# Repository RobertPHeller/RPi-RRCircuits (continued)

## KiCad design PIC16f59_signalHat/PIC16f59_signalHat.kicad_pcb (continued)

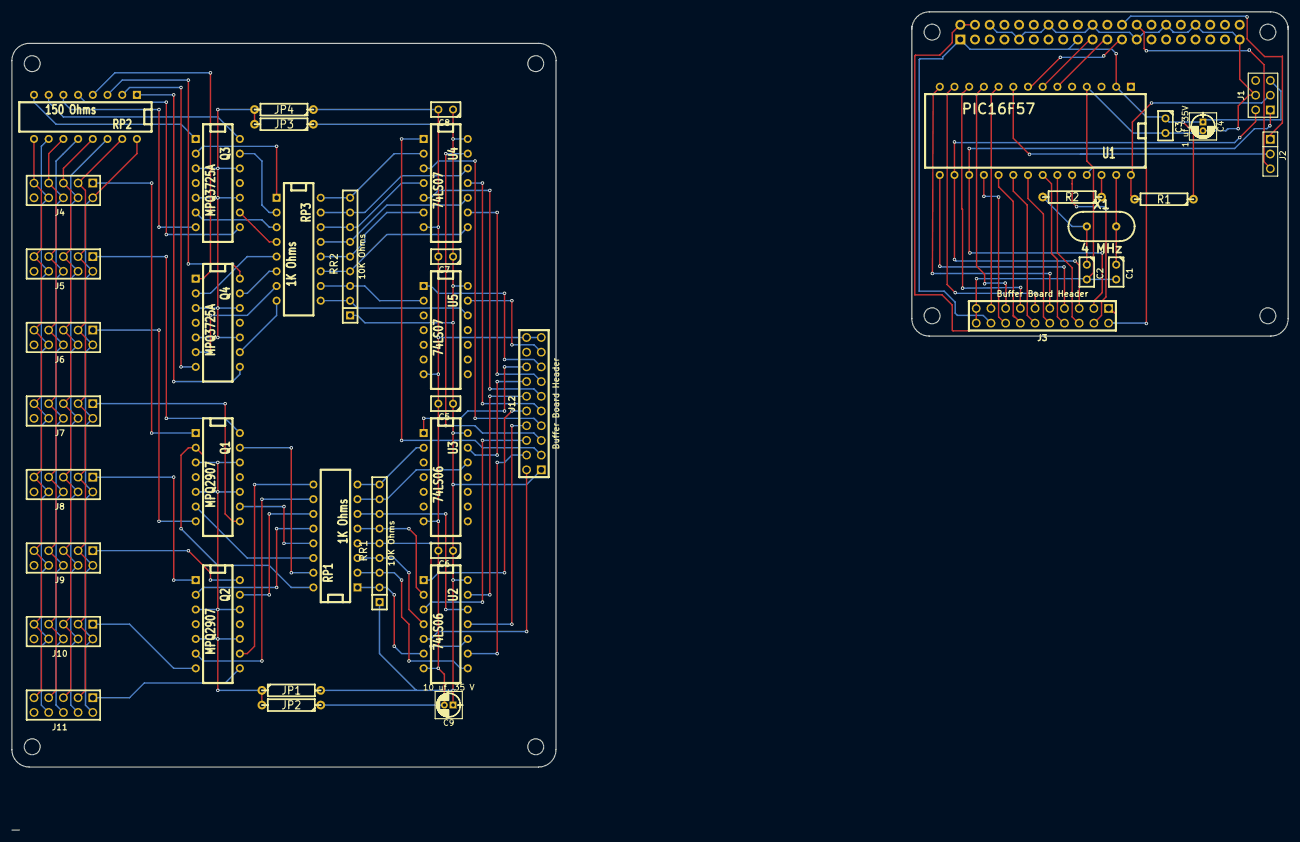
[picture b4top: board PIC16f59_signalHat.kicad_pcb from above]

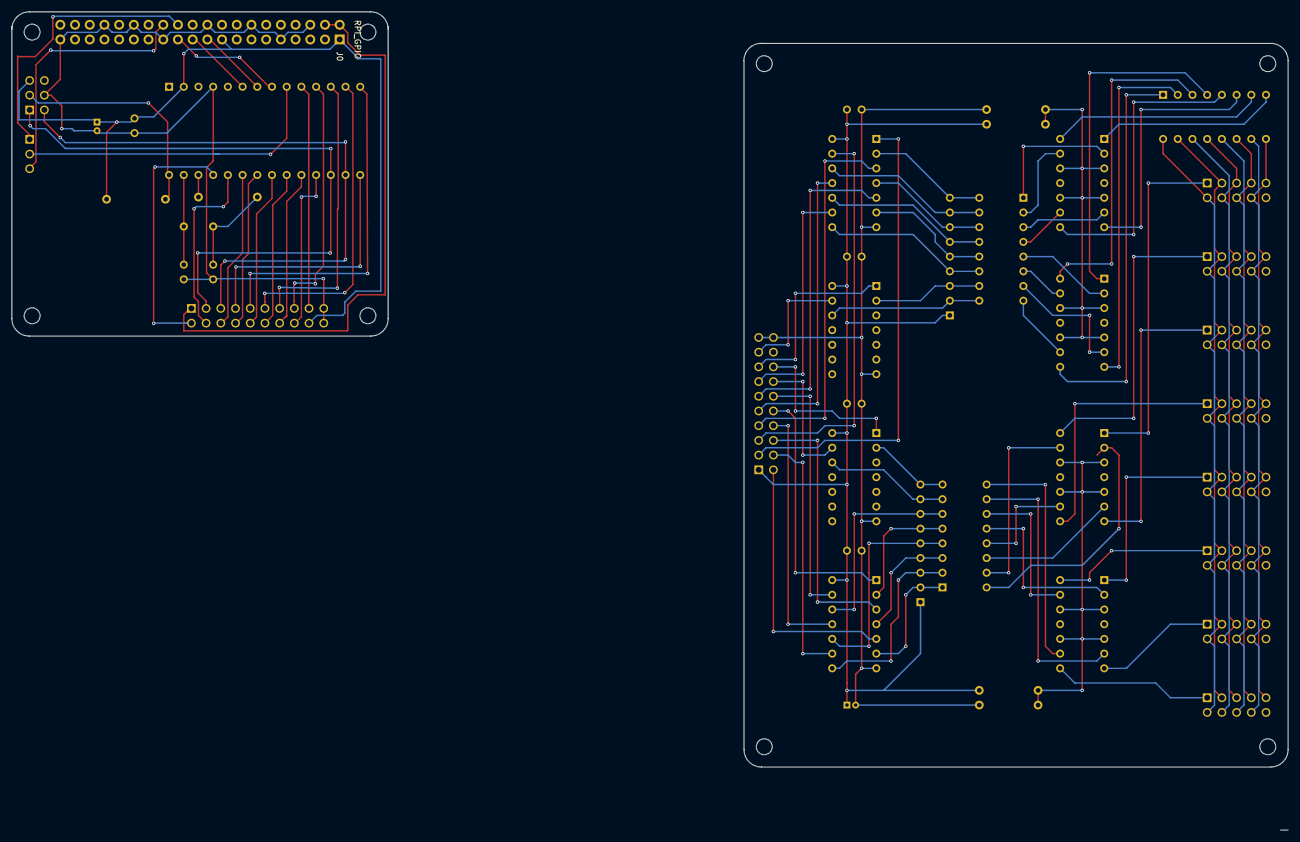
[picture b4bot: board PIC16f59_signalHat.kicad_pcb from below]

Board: 2 copper layers, 220.5 x 141.3 mm, 51 parts (9 on the bottom side), 105 nets.

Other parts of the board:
H1, H2, H3, H4, H4#2, H4#3, H4#4, H4#5: RPi_Hat_Mounting_Hole

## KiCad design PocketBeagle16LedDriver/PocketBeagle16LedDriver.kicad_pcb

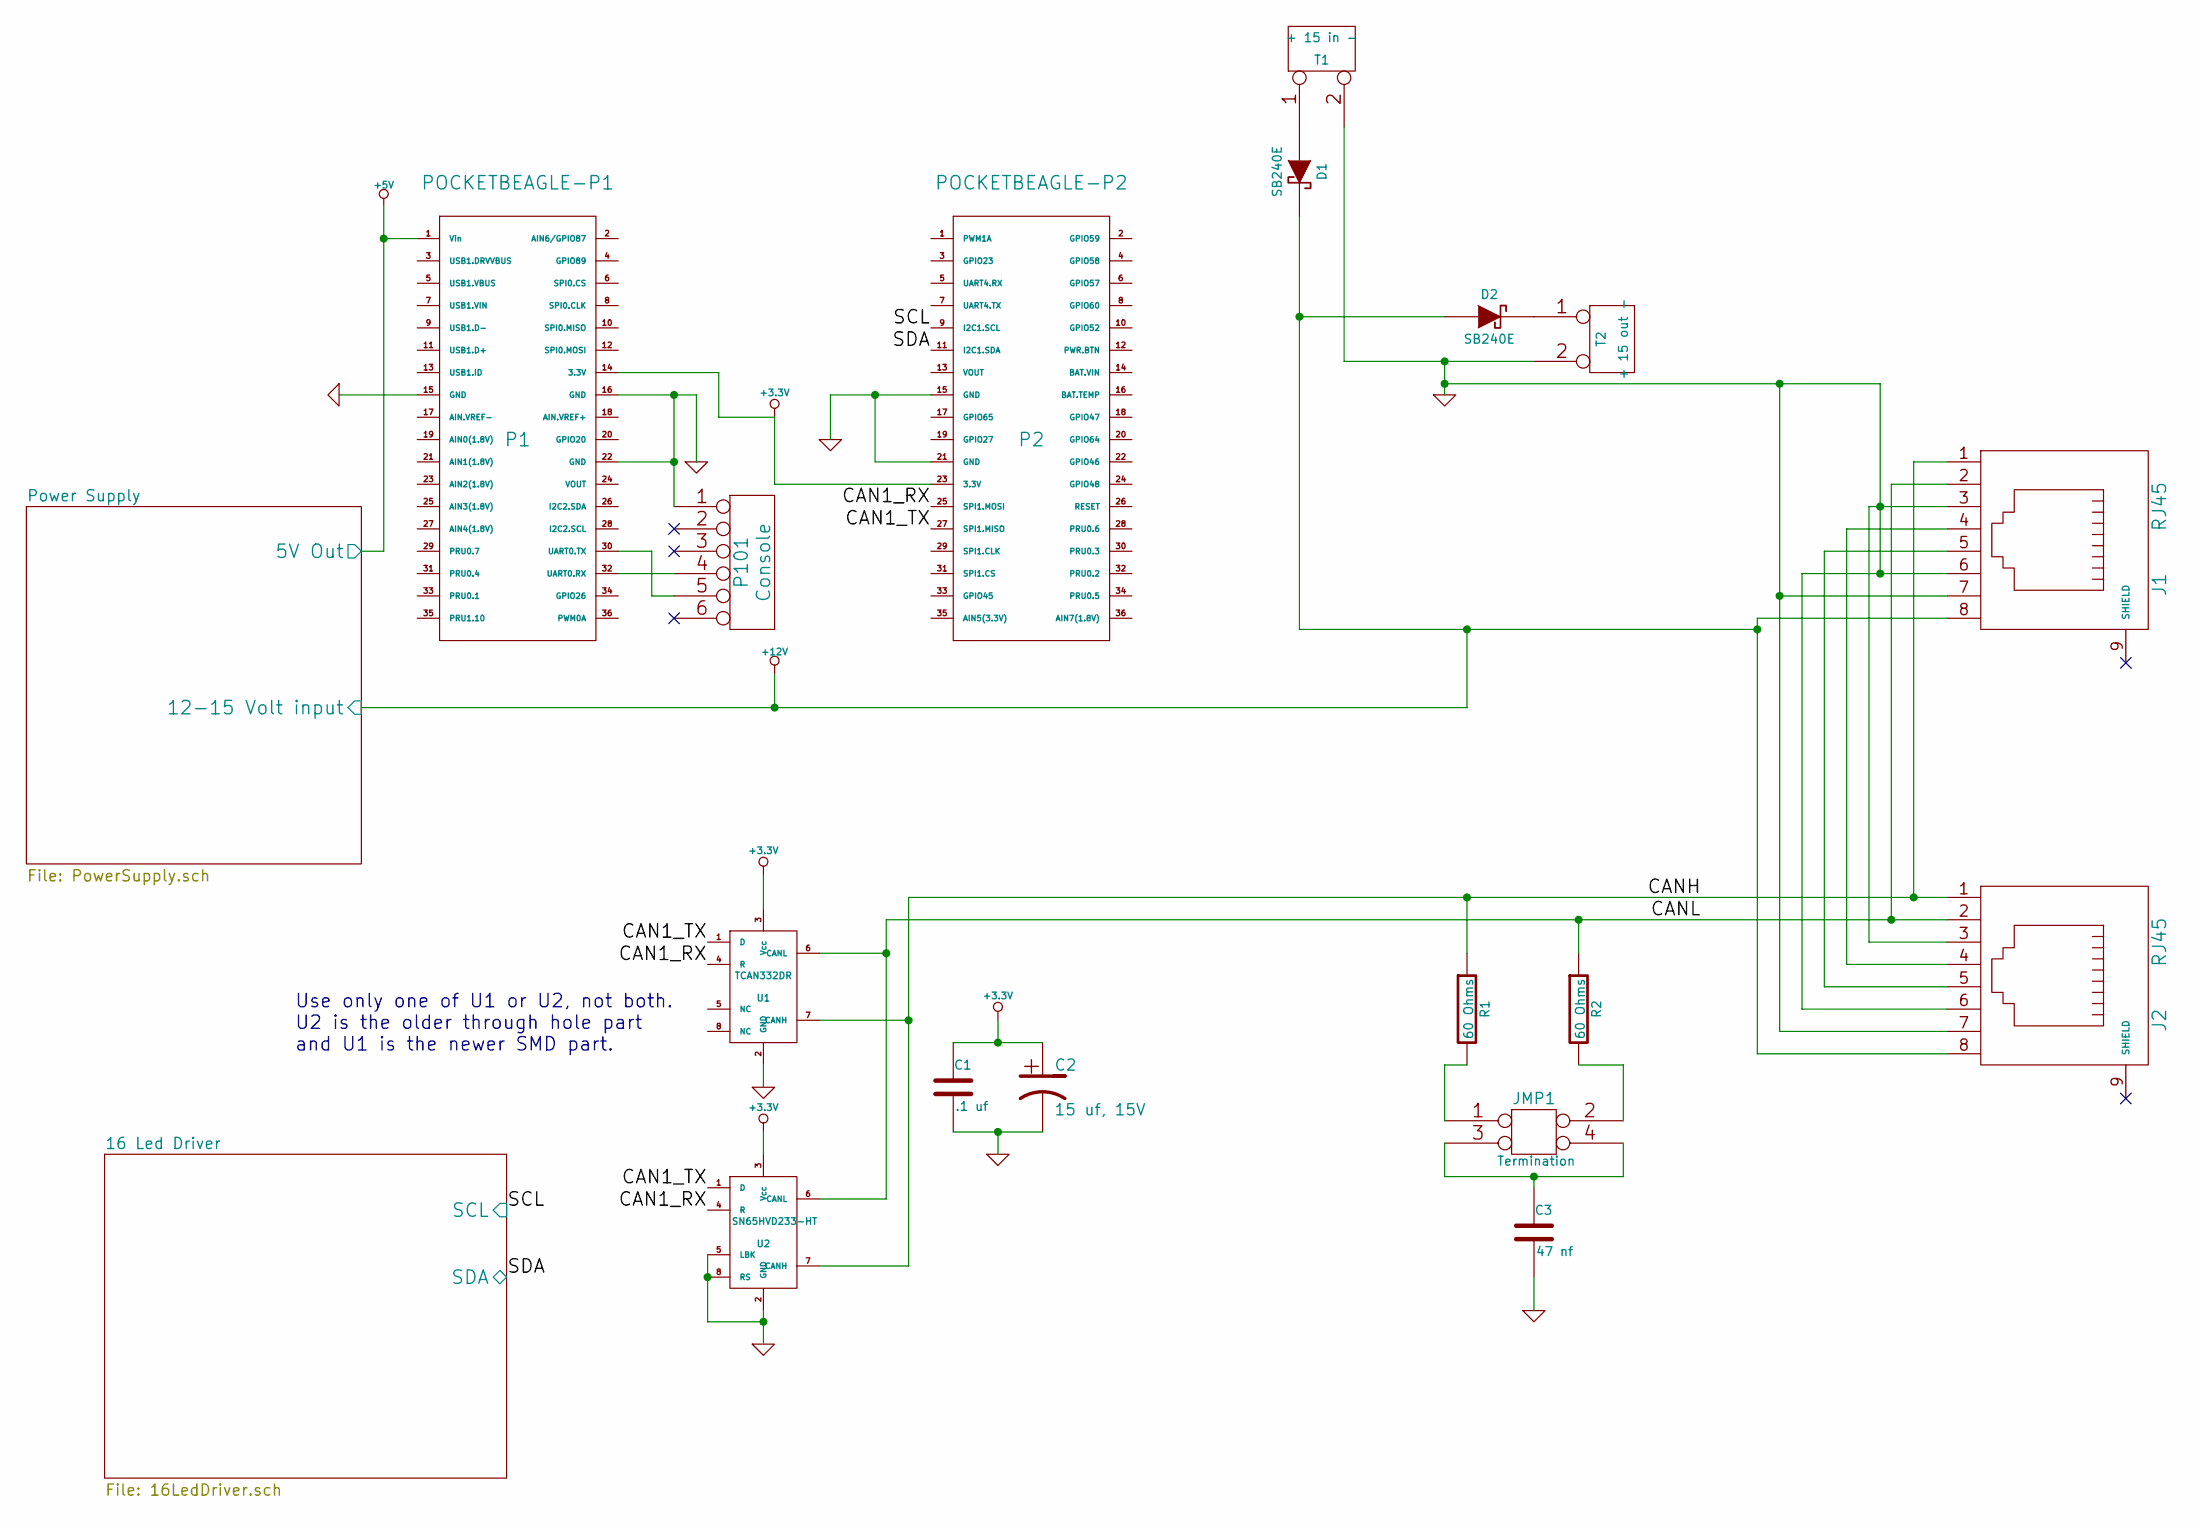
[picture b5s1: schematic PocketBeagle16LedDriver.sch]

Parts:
C1: .1 uf
C2: 15 uf, 15V
C3: 47 nf
D1, D2: SB240E
J1, J2: RJ45
JMP1: Termination
P1: POCKETBEAGLE-P1
P2: POCKETBEAGLE-P2
P101: Console
R1, R2: 60 Ohms
T1: + 15 in -
T2: + 15 out -
U1: TCAN332DR
U2: SN65HVD233-HT

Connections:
+3.3V: C1.1, C2.1, P1.14 (3.3V), P2.23 (3.3V), U1.3 (Vcc), U2.3 (Vcc); also elsewhere on the board
+5V: P1.1 (Vin); also elsewhere on the board
+12V: D1.2 (K), D2.1 (A), J1.8, J2.8; also elsewhere on the board
/16 Led Driver/SCL: P2.9 (I2C1.SCL); also elsewhere on the board
/16 Led Driver/SDA: P2.11 (I2C1.SDA); also elsewhere on the board
/CAN1_RX: P2.25 (SPI1.MOSI), U1.4 (R), U2.4 (R)
/CAN1_TX: P2.27 (SPI1.MISO), U1.1 (D), U2.1 (D)
/CANH: J1.1, J2.1, R1.1, U1.7 (CANH), U2.7 (CANH)
/CANL: J1.2, J2.2, R2.1, U1.6 (CANL), U2.6 (CANL)
GND: C1.2, C2.2, C3.2, J1.3, J1.6, J1.7, J2.3, J2.6, J2.7, P1.15 (GND), P1.16 (GND), P1.22 (GND), P2.15 (GND), P2.21 (GND), P101.1, T1.2 (PM), T2.2 (PM), U1.2 (GND), U2.2 (GND), U2.5 (LBK), U2.8 (RS); also elsewhere on the board
unnamed: J1.4, J2.4
unnamed: J1.5, J2.5
unnamed: P1.32 (UART0.RX), P101.4
unnamed: P1.30 (UART0.TX), P101.5
unnamed: JMP1.1, R1.2
unnamed: JMP1.2, R2.2
unnamed: C3.1, JMP1.3, JMP1.4
unnamed: D1.1 (A), T1.1
unnamed: D2.2 (K), T2.1

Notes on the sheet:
Use only one of U1 or U2, not both. U2 is the older through hole part and U1 is the newer SMD part.

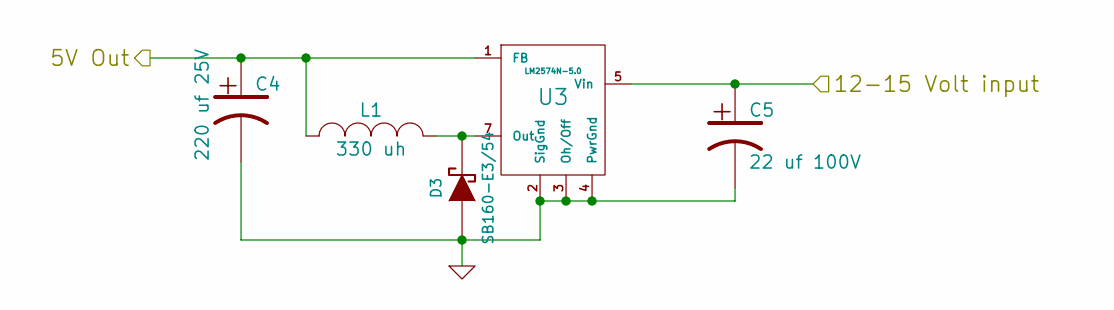
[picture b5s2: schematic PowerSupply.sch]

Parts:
C4: 220 uf 25V; C1-3V8; Part Number REA221M1EBK-0811P
C5: 22 uf 100V; C1-3V8; Part Number REA220M2ABK-0811P
D3: SB160-E3/54; DO-41; Part Number SB160-E3/54
L1: 330 uh; PE-LowProfile; Part Number PE-52627NL
U3: LM2574N-5.0

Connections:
+5V: C4.1, L1.1, U3.1 (FB); also elsewhere on the board
+12V: C5.1, U3.5 (Vin); also elsewhere on the board
GND: C4.2, C5.2, D3.1 (A), U3.2 (SigGnd), U3.3 (Oh/Off), U3.4 (PwrGnd); also elsewhere on the board
unnamed: D3.2 (K), L1.2, U3.7 (Out)

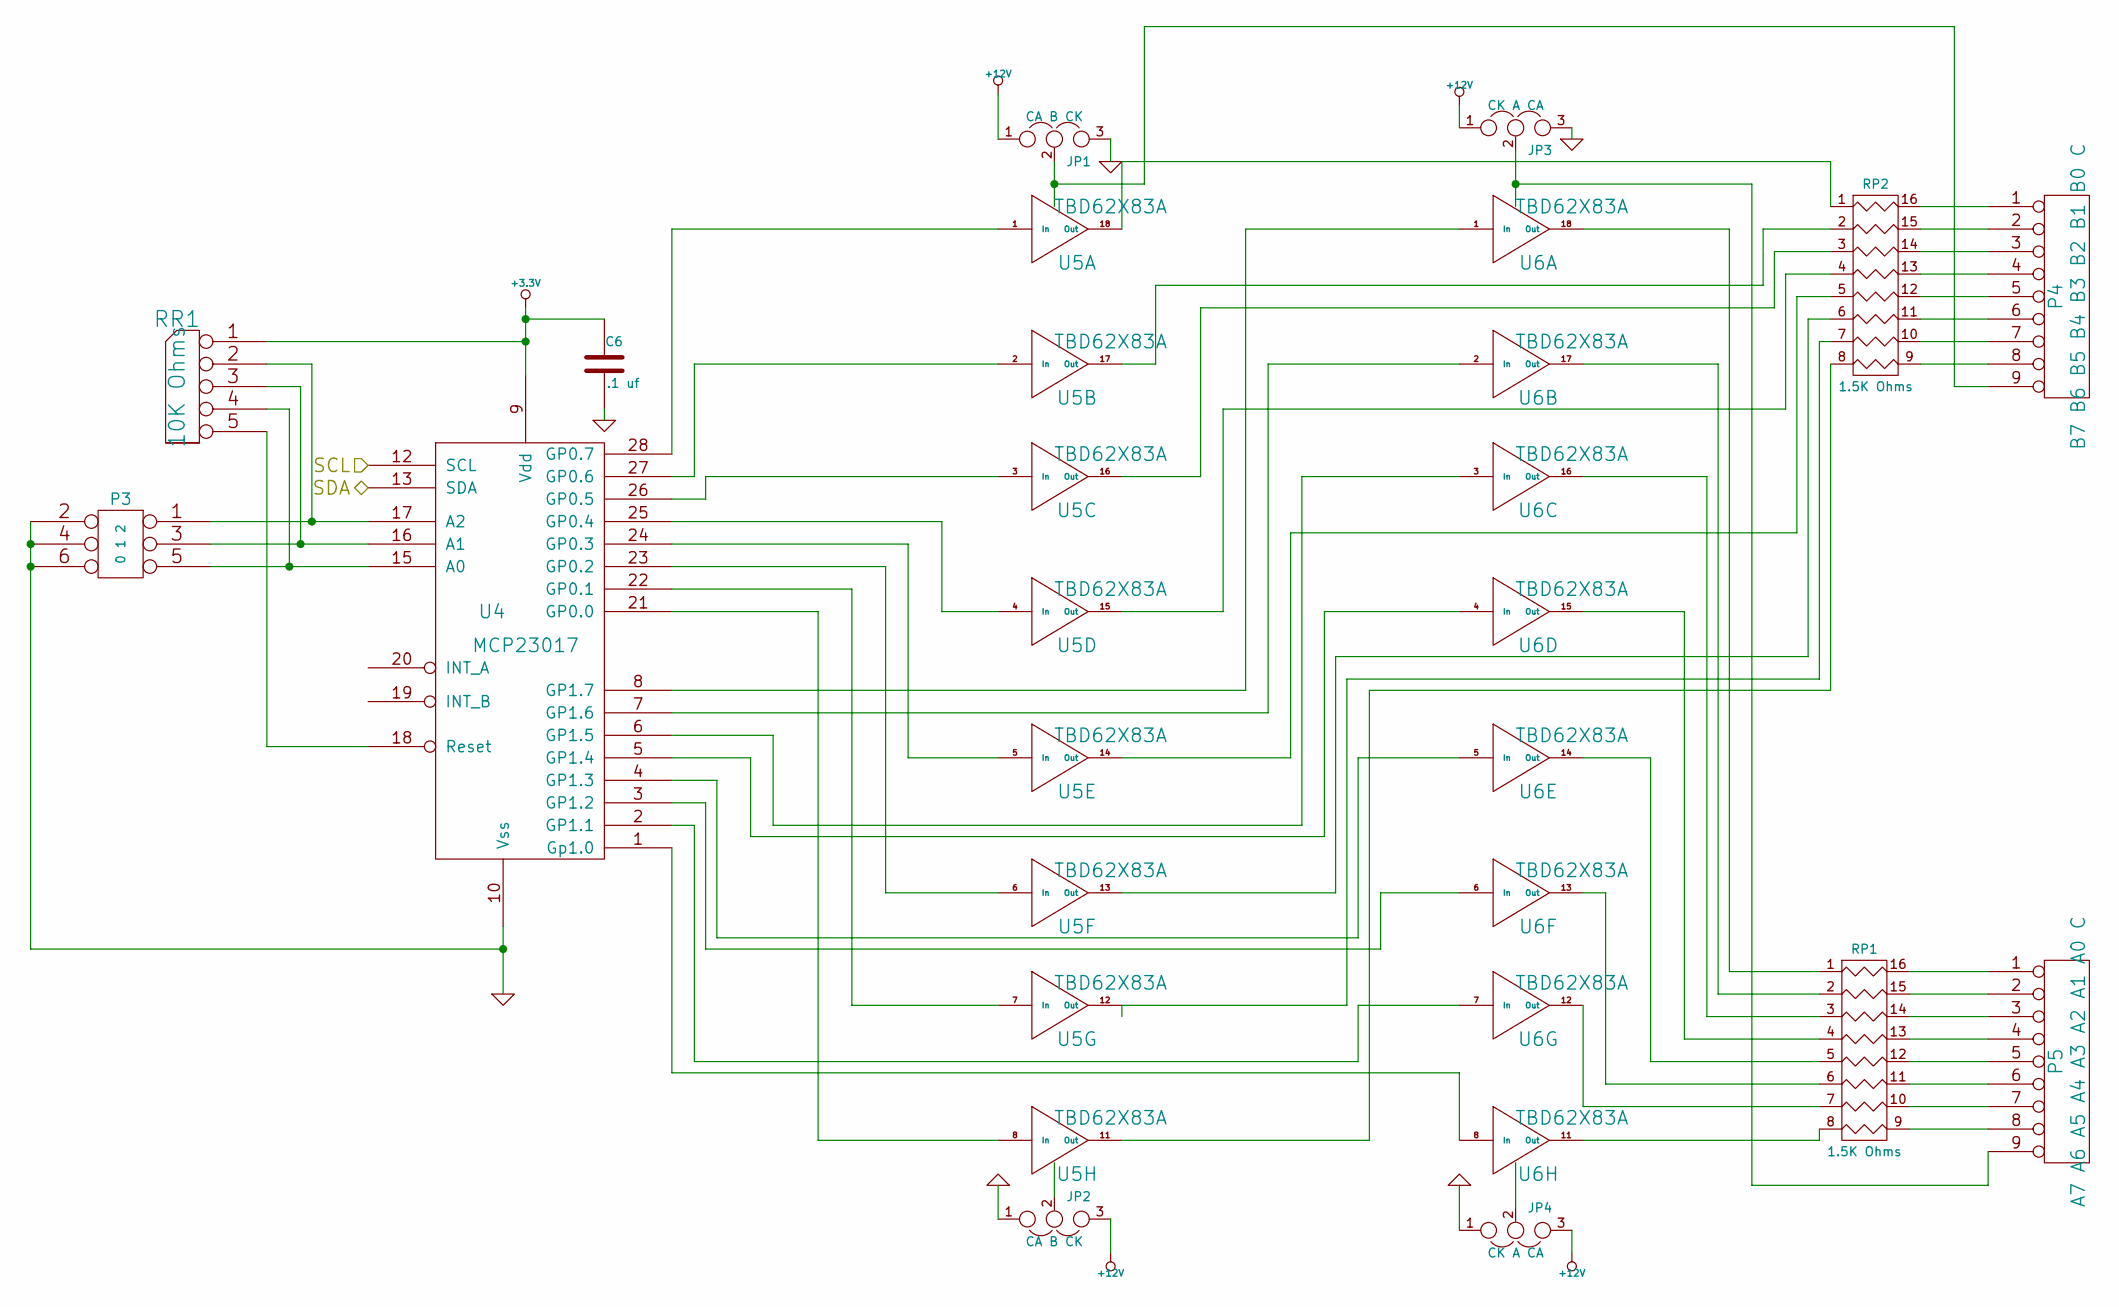
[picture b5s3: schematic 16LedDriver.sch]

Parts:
C6: .1 uf
JP1, JP2: CA B CK
JP3, JP4: CK A CA
P3: 0 1 2
P4: B7 B6 B5 B4 B3 B2 B1 B0 C
P5: A7 A6 A5 A4 A3 A2 A1 A0 C
RP1, RP2: 1.5K Ohms
RR1: 10K Ohms
U4: MCP23017
U5, U6: TBD62X83A

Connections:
+3.3V: C6.1, RR1.1 (COM), U4.9 (Vdd); also elsewhere on the board
+12V: JP1.1, JP2.3, JP3.1, JP4.3; also elsewhere on the board
/16 Led Driver/SCL: U4.12 (SCL); also elsewhere on the board
/16 Led Driver/SDA: U4.13 (SDA); also elsewhere on the board
GND: C6.2, JP1.3, JP2.1, JP3.3, JP4.1, P3.2, P3.4, P3.6, U4.10 (Vss); also elsewhere on the board
unnamed: U4.4 (GP1.3), U6.5 (In)
unnamed: U4.3 (GP1.2), U6.6 (In)
unnamed: U4.5 (GP1.4), U6.4 (In)
unnamed: U4.6 (GP1.5), U6.3 (In)
unnamed: RP2.3, U5.16 (Out)
unnamed: RP2.2, U5.17 (Out)
unnamed: RP2.1, U5.18 (Out)
unnamed: JP4.2, U6.9 (IC)
unnamed: JP2.2, U5.9 (IC)
unnamed: U4.1 (Gp1.0), U6.8 (In)
unnamed: U4.2 (GP1.1), U6.7 (In)
unnamed: U4.27 (GP0.6), U5.2 (In)
unnamed: U4.28 (GP0.7), U5.1 (In)
unnamed: U4.23 (GP0.2), U5.6 (In)
unnamed: U4.7 (GP1.6), U6.2 (In)
unnamed: U4.8 (GP1.7), U6.1 (In)
unnamed: U4.21 (GP0.0), U5.8 (In)
unnamed: U4.22 (GP0.1), U5.7 (In)
unnamed: U4.24 (GP0.3), U5.5 (In)
unnamed: U4.25 (GP0.4), U5.4 (In)
unnamed: U4.26 (GP0.5), U5.3 (In)
unnamed: P5.6, RP1.11 (R6)
unnamed: JP3.2, P5.9, U6.10 (OC)
unnamed: JP1.2, P4.9, U5.10 (OC)
unnamed: P5.8, RP1.9 (R8)
unnamed: P5.7, RP1.10 (R7)
unnamed: P5.5, RP1.12 (R5)
unnamed: P5.4, RP1.13 (R4)
unnamed: P5.3, RP1.14 (R3)
unnamed: P5.2, RP1.15 (R2)
unnamed: P5.1, RP1.16 (R1)
unnamed: P4.8, RP2.9 (R8)
unnamed: P4.7, RP2.10 (R7)
unnamed: P4.6, RP2.11 (R6)
unnamed: P4.5, RP2.12 (R5)
unnamed: P4.4, RP2.13 (R4)
unnamed: P4.3, RP2.14 (R3)
unnamed: RR1.5, U4.18 (Reset)
unnamed: P3.1, RR1.2, U4.17 (A2)
unnamed: P3.3, RR1.3, U4.16 (A1)
unnamed: P3.5, RR1.4, U4.15 (A0)
unnamed: P4.2, RP2.15 (R2)
unnamed: RP2.8, U5.11 (Out)
unnamed: RP2.7, U5.12 (Out)
unnamed: RP2.6, U5.13 (Out)
unnamed: RP1.8, U6.11 (Out)
unnamed: RP2.5, U5.14 (Out)
unnamed: RP2.4, U5.15 (Out)
unnamed: RP1.4, U6.15 (Out)
unnamed: P4.1, RP2.16 (R1)
unnamed: RP1.1, U6.18 (Out)
unnamed: RP1.2, U6.17 (Out)
unnamed: RP1.3, U6.16 (Out)
unnamed: RP1.5, U6.14 (Out)
unnamed: RP1.6, U6.13 (Out)
unnamed: RP1.7, U6.12 (Out)

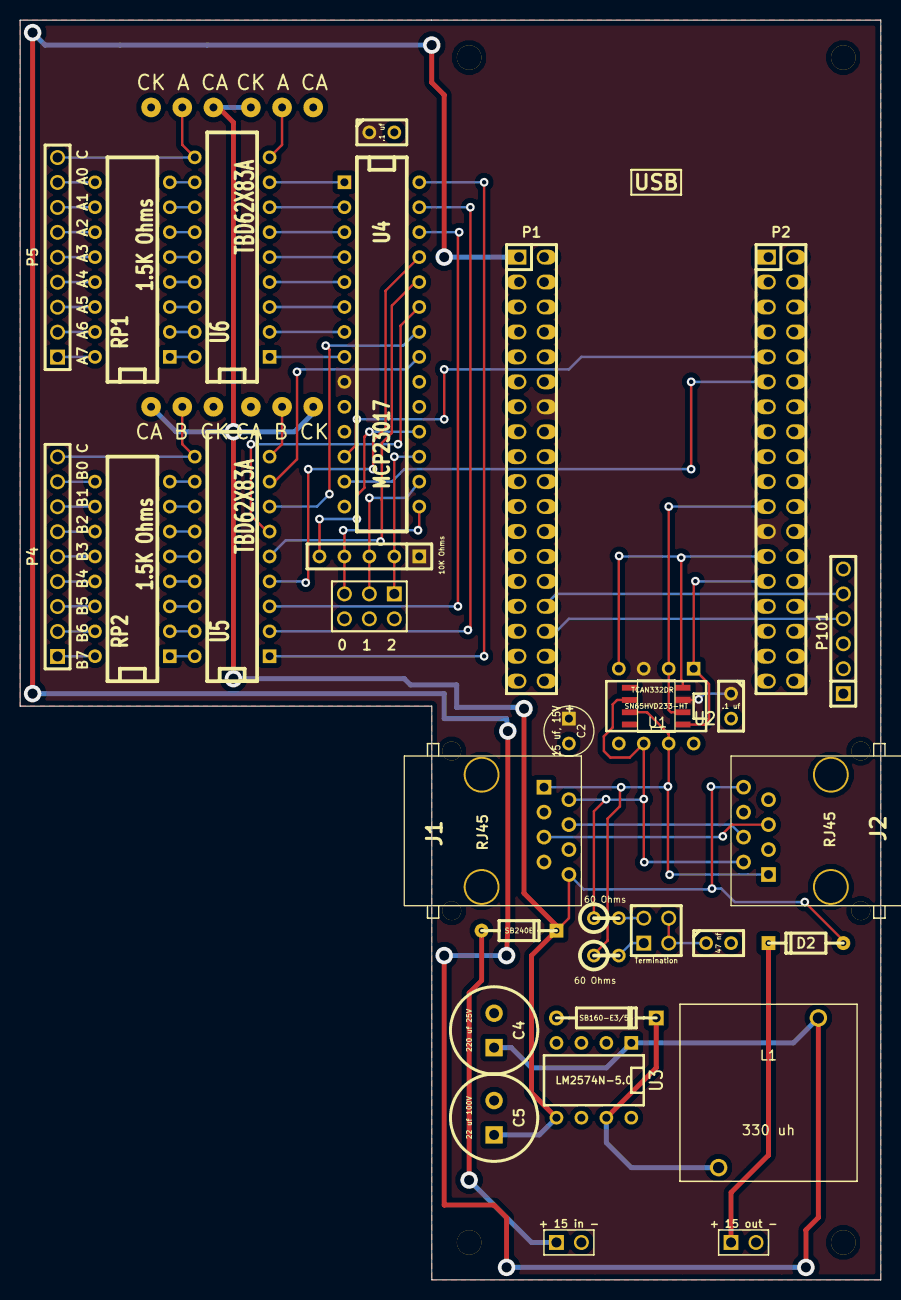
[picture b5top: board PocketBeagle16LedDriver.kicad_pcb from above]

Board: 2 copper layers, 87.6 x 128.3 mm, 40 parts (0 on the bottom side), 76 nets.

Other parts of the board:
MH: MountingHole_2-5mm_RevA_Date21Jun2010
MH#2, MH#3, MH#4: MountingHole_2-5mm_RevA_Date21Jun2010

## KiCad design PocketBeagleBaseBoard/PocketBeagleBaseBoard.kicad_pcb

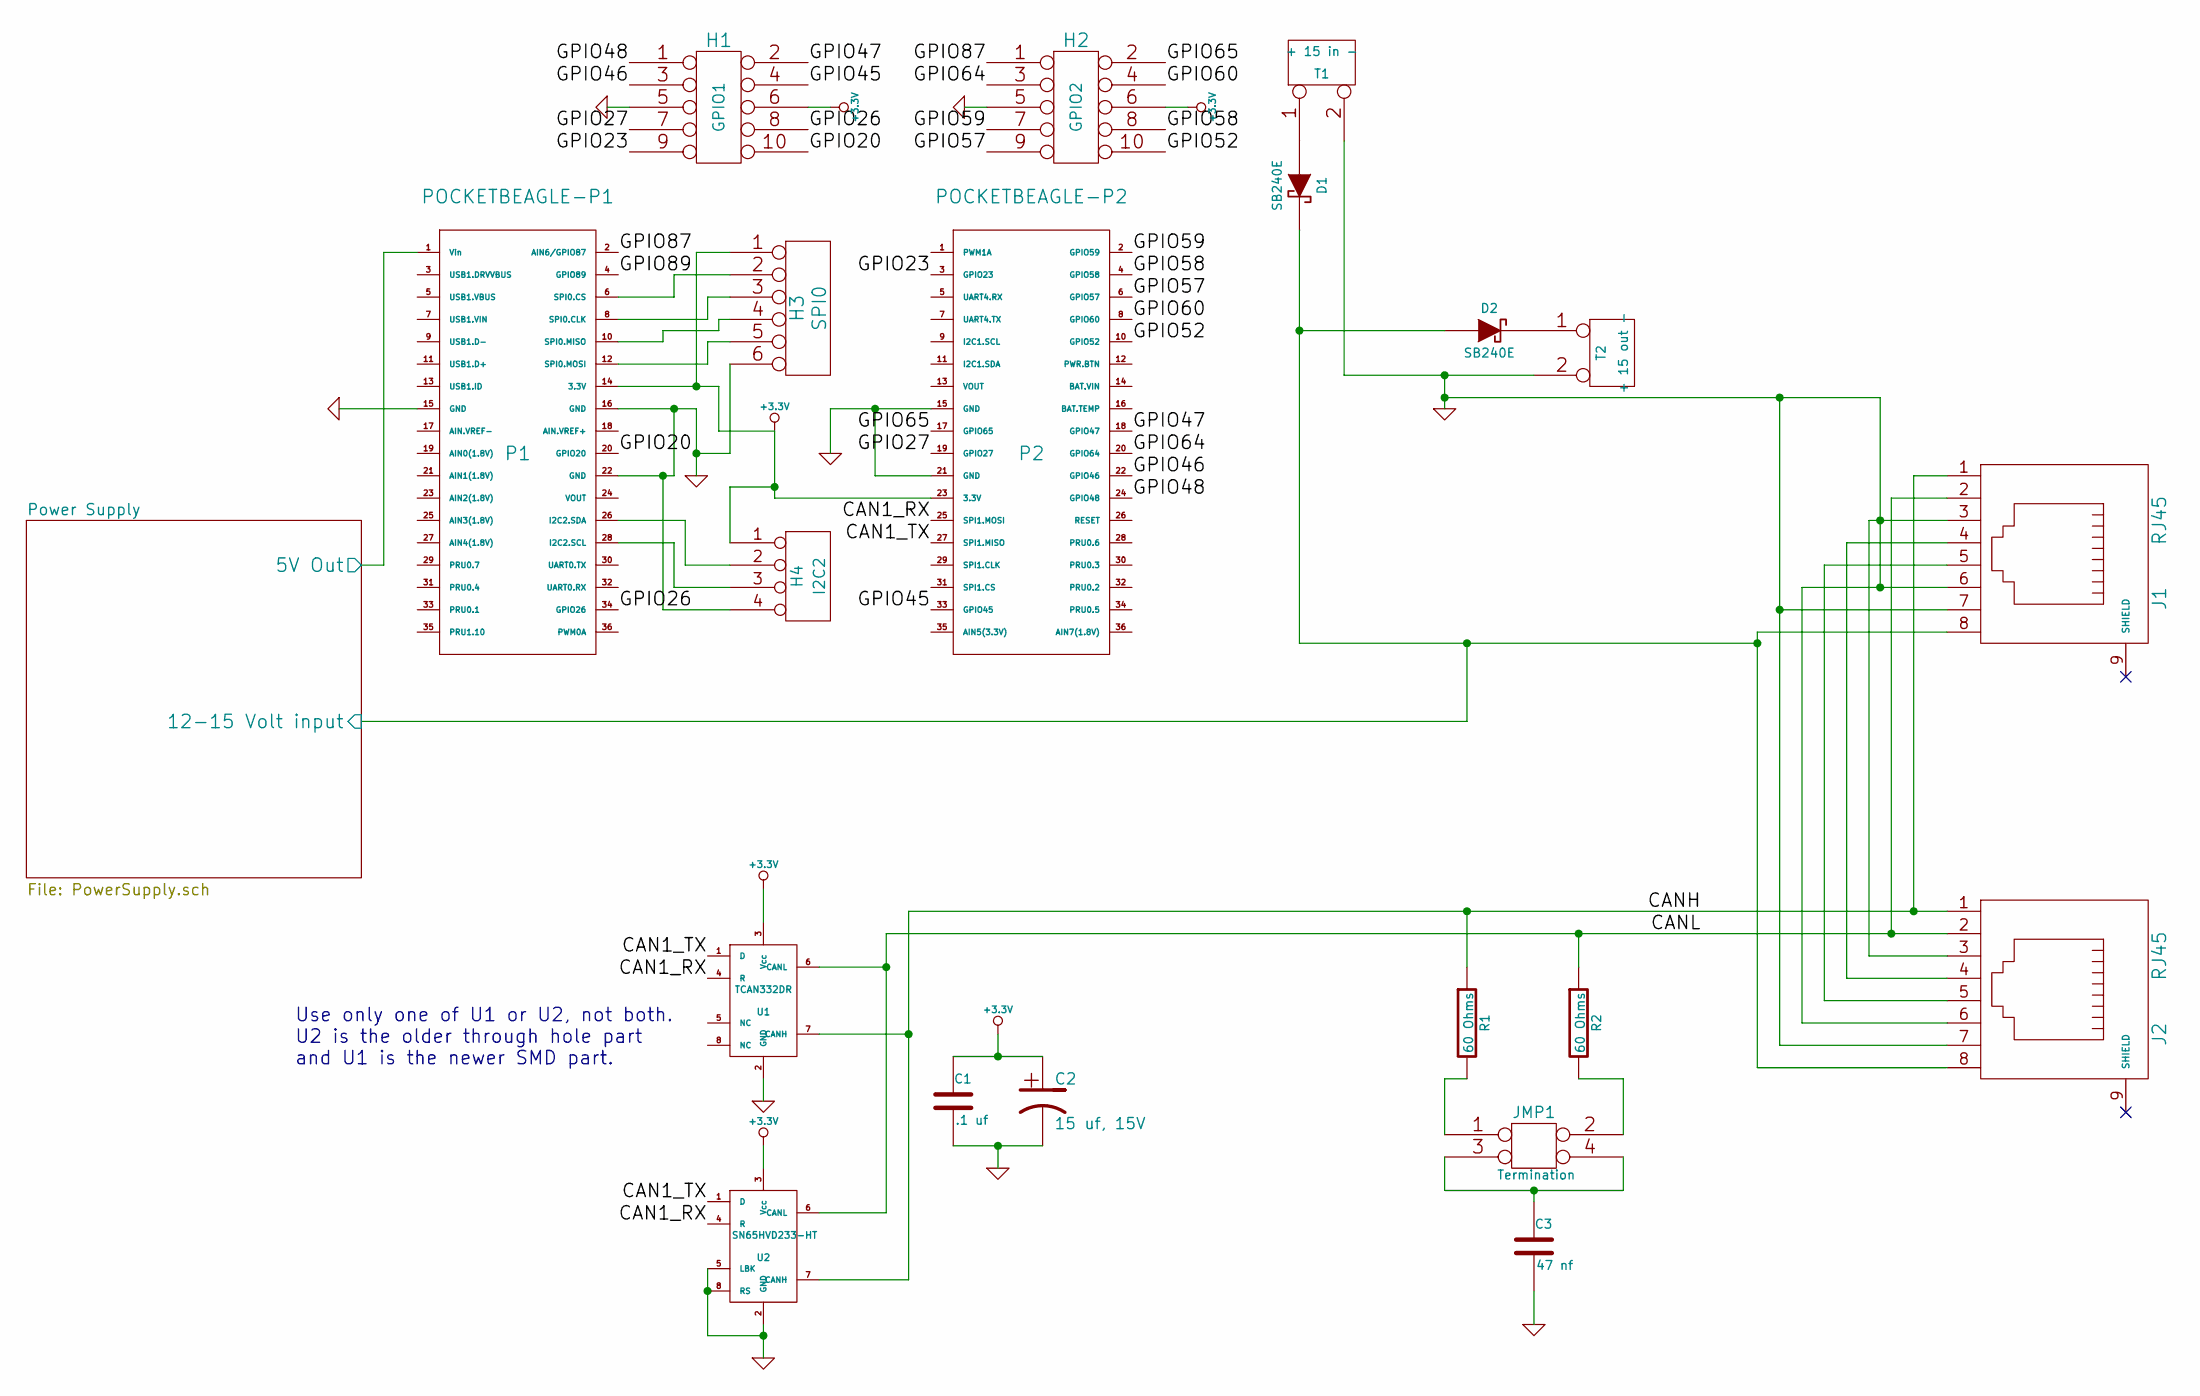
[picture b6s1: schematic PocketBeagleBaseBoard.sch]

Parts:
C1: .1 uf
C2: 15 uf, 15V
C3: 47 nf
D1, D2: SB240E
H1: GPIO1
H2: GPIO2
H3: SPI0
H4: I2C2
J1, J2: RJ45
JMP1: Termination
P1: POCKETBEAGLE-P1
P2: POCKETBEAGLE-P2
R1, R2: 60 Ohms
T1: + 15 in -
T2: + 15 out -
U1: TCAN332DR
U2: SN65HVD233-HT

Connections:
+3.3V: C1.1, C2.1, H1.6, H2.6, H3.1, H4.1, P1.14 (3.3V), P2.23 (3.3V), U1.3 (Vcc), U2.3 (Vcc)
/CAN1_RX: P2.25 (SPI1.MOSI), U1.4 (R), U2.4 (R)
/CAN1_TX: P2.27 (SPI1.MISO), U1.1 (D), U2.1 (D)
/CANH: J1.1, J2.1, R1.1, U1.7 (CANH), U2.7 (CANH)
/CANL: J1.2, J2.2, R2.1, U1.6 (CANL), U2.6 (CANL)
/GPIO20: H1.10, P1.20 (GPIO20)
/GPIO23: H1.9, P2.3 (GPIO23)
/GPIO26: H1.8, P1.34 (GPIO26)
/GPIO27: H1.7, P2.19 (GPIO27)
/GPIO45: H1.4, P2.33 (GPIO45)
/GPIO46: H1.3, P2.22 (GPIO46)
/GPIO47: H1.2, P2.18 (GPIO47)
/GPIO48: H1.1, P2.24 (GPIO48)
/GPIO52: H2.10, P2.10 (GPIO52)
/GPIO57: H2.9, P2.6 (GPIO57)
/GPIO58: H2.8, P2.4 (GPIO58)
/GPIO59: H2.7, P2.2 (GPIO59)
/GPIO60: H2.4, P2.8 (GPIO60)
/GPIO64: H2.3, P2.20 (GPIO64)
/GPIO65: H2.2, P2.17 (GPIO65)
/GPIO87: H2.1, P1.2 (AIN6/GPIO87)
/Power Supply/5V Out: P1.1 (Vin); also elsewhere on the board
/Power Supply/12-15 Volt input: D1.2 (K), D2.1 (A), J1.8, J2.8; also elsewhere on the board
GND: C1.2, C2.2, C3.2, H1.5, H2.5, H3.6, H4.4, J1.3, J1.6, J1.7, J2.3, J2.6, J2.7, P1.15 (GND), P1.16 (GND), P1.22 (GND), P2.15 (GND), P2.21 (GND), T1.2 (PM), T2.2 (PM), U1.2 (GND), U2.2 (GND), U2.5 (LBK), U2.8 (RS); also elsewhere on the board
unnamed: JMP1.1, R1.2
unnamed: JMP1.2, R2.2
unnamed: C3.1, JMP1.3, JMP1.4
unnamed: H3.3, P1.8 (SPI0.CLK)
unnamed: H3.2, P1.6 (SPI0.CS)
unnamed: H4.3, P1.28 (I2C2.SCL)
unnamed: H4.2, P1.26 (I2C2.SDA)
unnamed: H3.5, P1.12 (SPI0.MOSI)
unnamed: H3.4, P1.10 (SPI0.MISO)
unnamed: J1.5, J2.5
unnamed: J1.4, J2.4
unnamed: D1.1 (A), T1.1
unnamed: D2.2 (K), T2.1

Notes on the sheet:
Use only one of U1 or U2, not both. U2 is the older through hole part and U1 is the newer SMD part.

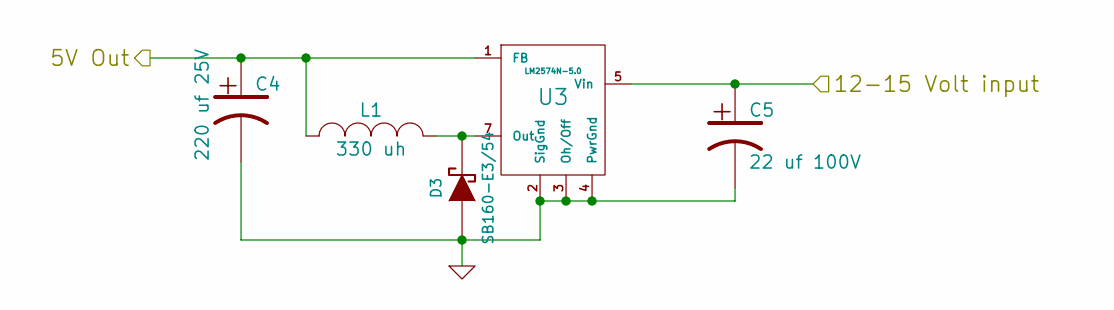
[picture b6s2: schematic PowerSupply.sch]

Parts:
C4: 220 uf 25V; C1-3V8; Part Number REA221M1EBK-0811P
C5: 22 uf 100V; C1-3V8; Part Number REA220M2ABK-0811P
D3: SB160-E3/54; DO-41; Part Number SB160-E3/54
L1: 330 uh; PE-LowProfile; Part Number PE-52627NL
U3: LM2574N-5.0

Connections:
/Power Supply/5V Out: C4.1, L1.1, U3.1 (FB); also elsewhere on the board
/Power Supply/12-15 Volt input: C5.1, U3.5 (Vin); also elsewhere on the board
GND: C4.2, C5.2, D3.1 (A), U3.2 (SigGnd), U3.3 (Oh/Off), U3.4 (PwrGnd); also elsewhere on the board
unnamed: D3.2 (K), L1.2, U3.7 (Out)

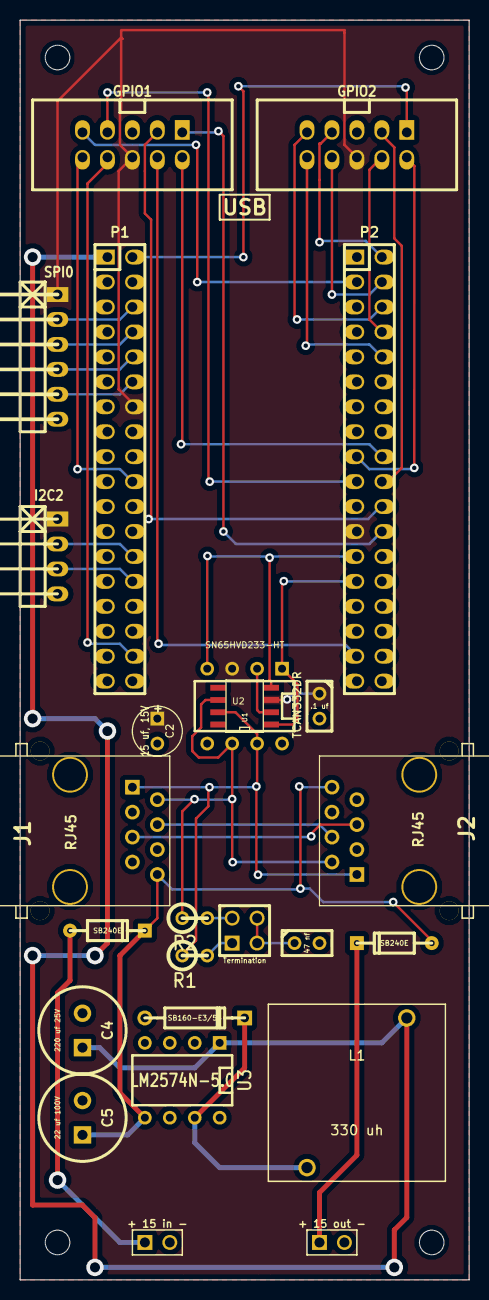
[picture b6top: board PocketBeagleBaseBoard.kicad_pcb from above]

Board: 2 copper layers, 45.7 x 128.3 mm, 29 parts (0 on the bottom side), 38 nets.

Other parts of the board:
MH: MountingHole_2-5mm_RevA_Date21Jun2010
MH#2, MH#3, MH#4: MountingHole_2-5mm_RevA_Date21Jun2010

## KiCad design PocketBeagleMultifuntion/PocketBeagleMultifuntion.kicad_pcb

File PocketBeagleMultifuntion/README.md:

# PocketBeagleMultifuntion

This is a circuit board that supports a PocketBeagle board to manage a range
of possible interlocking plants or other model railroad situations. It
contains four stall motor drivers with point sense, four CT Coil type
occupancy detectors, four Schmitt-Trigger inputs (for push buttons), four
driver outputs, 8 GPIO pins in a 5x2 header, and 16 PWM LED drivers. 
                                                  
The board contains these I/O sections:

- Four occupancy detectors.  These are current transformer based for DCC.
- Four stall-motor with point sense.
- Four Schmitt-Trigger inputs, typically for facia push buttons.
- Four driver outputs, typically for facia lamps (LEDs).
- Eight GPIO pins brought out to a 5x2 header.
- Sixteen PWM Led drivers.  These are meant to light lamps in signal heads. 

This board uses 24 GPIO pins and one I2C channel:

- **GPIO7** Occupancy Detector 1.
- **GPIO19** Occupancy Detector 2.
- **GPIO20** Occupancy Detector 3.
- **GPIO23** Occupancy Detector 4.
- **GPIO26** Motor Select 1: select the position of stall motor 1.
- **GPIO27** Motor Select 1: select the position of stall motor 2.
- **GPIO45** Motor Select 1: select the position of stall motor 3.
- **GPIO46** Motor Select 1: select the position of stall motor 4.
- **GPIO47** Point Sense 1: return the state of the points for stall motor 1.
- **GPIO48** Point Sense 1: return the state of the points for stall motor 2.
- **GPIO50** Point Sense 1: return the state of the points for stall motor 3.
- **GPIO52** Point Sense 1: return the state of the points for stall motor 4.
- **GPIO57** Schmitt trigger input 1.
- **GPIO58** Schmitt trigger input 2.
- **GPIO59** Schmitt trigger input 3.
- **GPIO60** Schmitt trigger input 4.
- **GPIO64** Driver (LED) 1.
- **GPIO65** Driver (LED) 2.
- **GPIO86** Driver (LED) 3.
- **GPIO87** Driver (LED) 4.
- **GPIO110** GPIO Line 1.
- **GPIO111** GPIO Line 2.
- **GPIO112** GPIO Line 3.
- **GPIO113** GPIO Line 4.
- **GPIO114** GPIO Line 5.
- **GPIO115** GPIO Line 6.
- **GPIO116** GPIO Line 7.
- **GPIO117** GPIO Line 8.
- **I2C1 Address 0x40** A PCA9685 16-channel, 12-bit PWM LED Controller

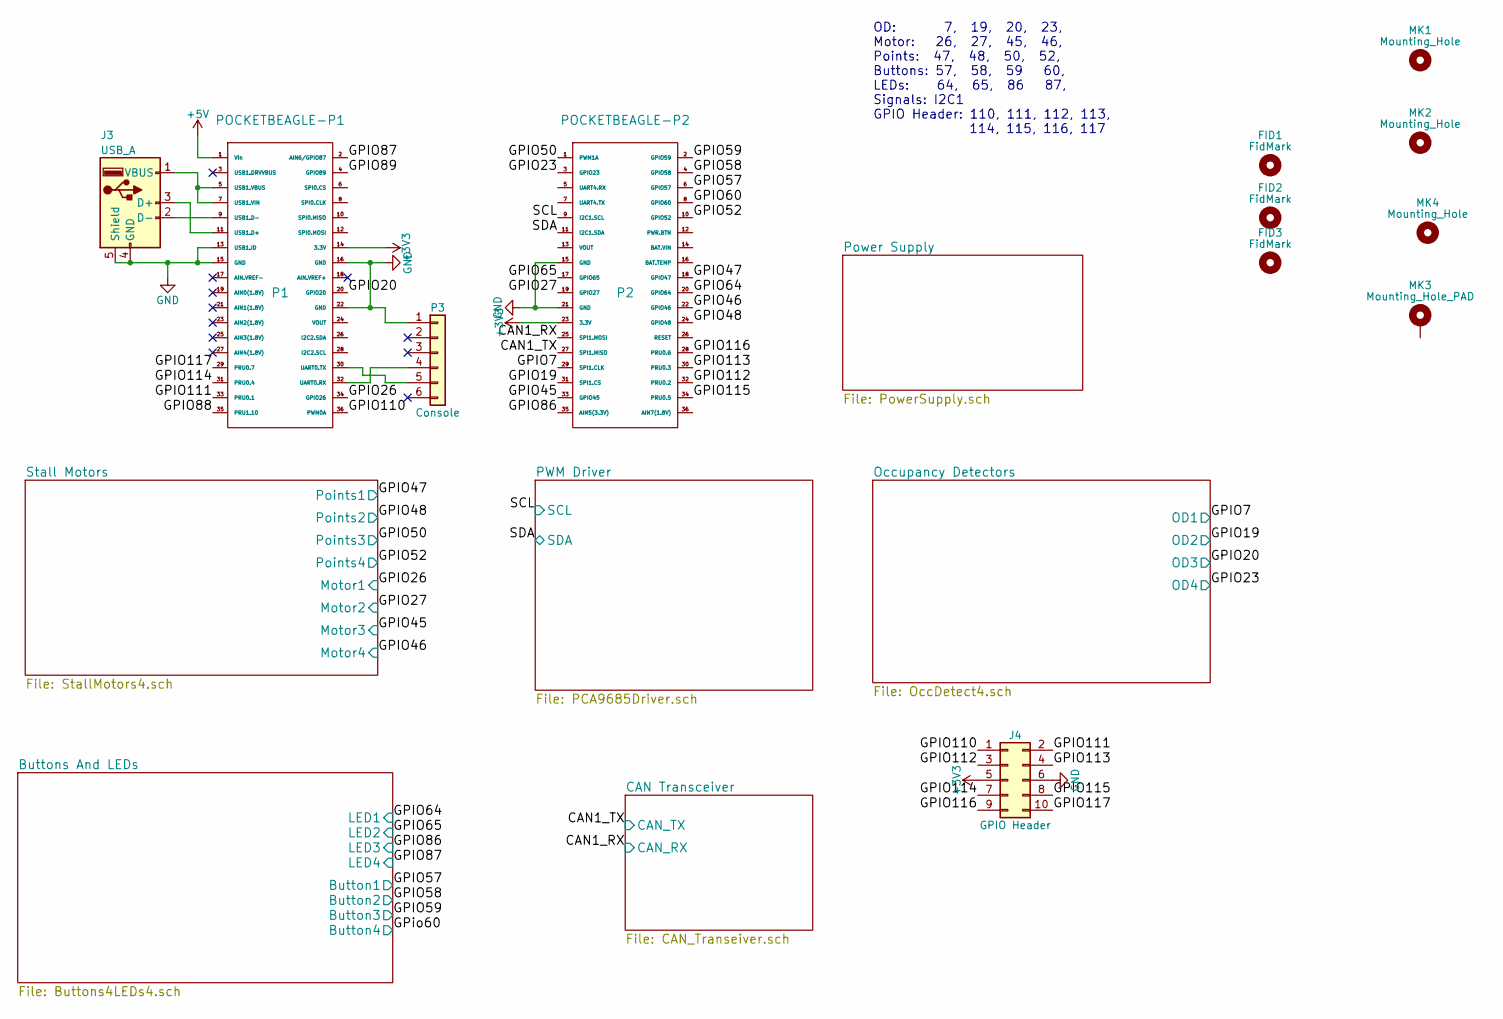
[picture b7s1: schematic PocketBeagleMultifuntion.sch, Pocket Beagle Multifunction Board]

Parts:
FID1, FID2, FID3: FidMark; Fiducial_1mm_Dia_2.54mm_Outer_CopperBottom
J3: USB_A
J4: GPIO Header; IDC_Header_Straight_10pins
MK1, MK2, MK4: Mounting_Hole; MountingHole_3.2mm_M3
MK3: Mounting_Hole_PAD; MountingHole_3.2mm_M3_Pad
P1: POCKETBEAGLE-P1
P2: POCKETBEAGLE-P2
P3: Console; Pin_Header_Straight_1x06_Pitch2.54mm

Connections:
+3V3: J4.5, P1.14 (3.3V), P2.23 (3.3V); also elsewhere on the board
+5V: P1.1 (Vin); also elsewhere on the board
/CAN1_RX: P2.25 (SPI1.MOSI); also elsewhere on the board
/CAN1_TX: P2.27 (SPI1.MISO); also elsewhere on the board
/GPIO7: P2.29 (SPI1.CLK); also elsewhere on the board
/GPIO19: P2.31 (SPI1.CS); also elsewhere on the board
/GPIO20: P1.20 (GPIO20); also elsewhere on the board
/GPIO23: P2.3 (GPIO23); also elsewhere on the board
/GPIO26: P1.34 (GPIO26); also elsewhere on the board
/GPIO27: P2.19 (GPIO27); also elsewhere on the board
/GPIO45: P2.33 (GPIO45); also elsewhere on the board
/GPIO46: P2.22 (GPIO46); also elsewhere on the board
/GPIO47: P2.18 (GPIO47); also elsewhere on the board
/GPIO48: P2.24 (GPIO48); also elsewhere on the board
/GPIO50: P2.1 (PWM1A); also elsewhere on the board
/GPIO52: P2.10 (GPIO52); also elsewhere on the board
/GPIO57: P2.6 (GPIO57); also elsewhere on the board
/GPIO58: P2.4 (GPIO58); also elsewhere on the board
/GPIO59: P2.2 (GPIO59); also elsewhere on the board
/GPIO60: P2.8 (GPIO60); also elsewhere on the board
/GPIO64: P2.20 (GPIO64); also elsewhere on the board
/GPIO65: P2.17 (GPIO65); also elsewhere on the board
/GPIO86: P2.35 (AIN5(3.3V)); also elsewhere on the board
/GPIO87: P1.2 (AIN6/GPIO87); also elsewhere on the board
/GPIO88: P1.35 (PRU1.10)
/GPIO89: P1.4 (GPIO89)
/GPIO110: J4.1, P1.36 (PWM0A)
/GPIO111: J4.2, P1.33 (PRU0.1)
/GPIO112: J4.3, P2.32 (PRU0.2)
/GPIO113: J4.4, P2.30 (PRU0.3)
/GPIO114: J4.7, P1.31 (PRU0.4)
/GPIO115: J4.8, P2.34 (PRU0.5)
/GPIO116: J4.9, P2.28 (PRU0.6)
/GPIO117: J4.10, P1.29 (PRU0.7)
/SCL: P2.9 (I2C1.SCL); also elsewhere on the board
/SDA: P2.11 (I2C1.SDA); also elsewhere on the board
GND: J3.4 (GND), J3.5 (Shield), J4.6, P1.13 (USB1.ID), P1.15 (GND), P1.16 (GND), P1.22 (GND), P2.15 (GND), P2.21 (GND), P3.1; also elsewhere on the board
unnamed: J3.1 (VBUS), P1.5 (USB1.VBUS), P1.7 (USB1.VIN)
unnamed: J3.2 (D-), P1.9 (USB1.D-)
unnamed: J3.3 (D+), P1.11 (USB1.D+)
unnamed: P1.30 (UART0.TX), P3.5
unnamed: P1.32 (UART0.RX), P3.4

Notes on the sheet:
OD: 7, 19, 20, 23, Motor: 26, 27, 45, 46, Points: 47, 48, 50, 52, Buttons: 57, 58, 59 60, LEDs: 64, 65, 86 87, Signals: I2C1 GPIO Header: 110, 111, 112, 113, 114, 115, 116, 117
